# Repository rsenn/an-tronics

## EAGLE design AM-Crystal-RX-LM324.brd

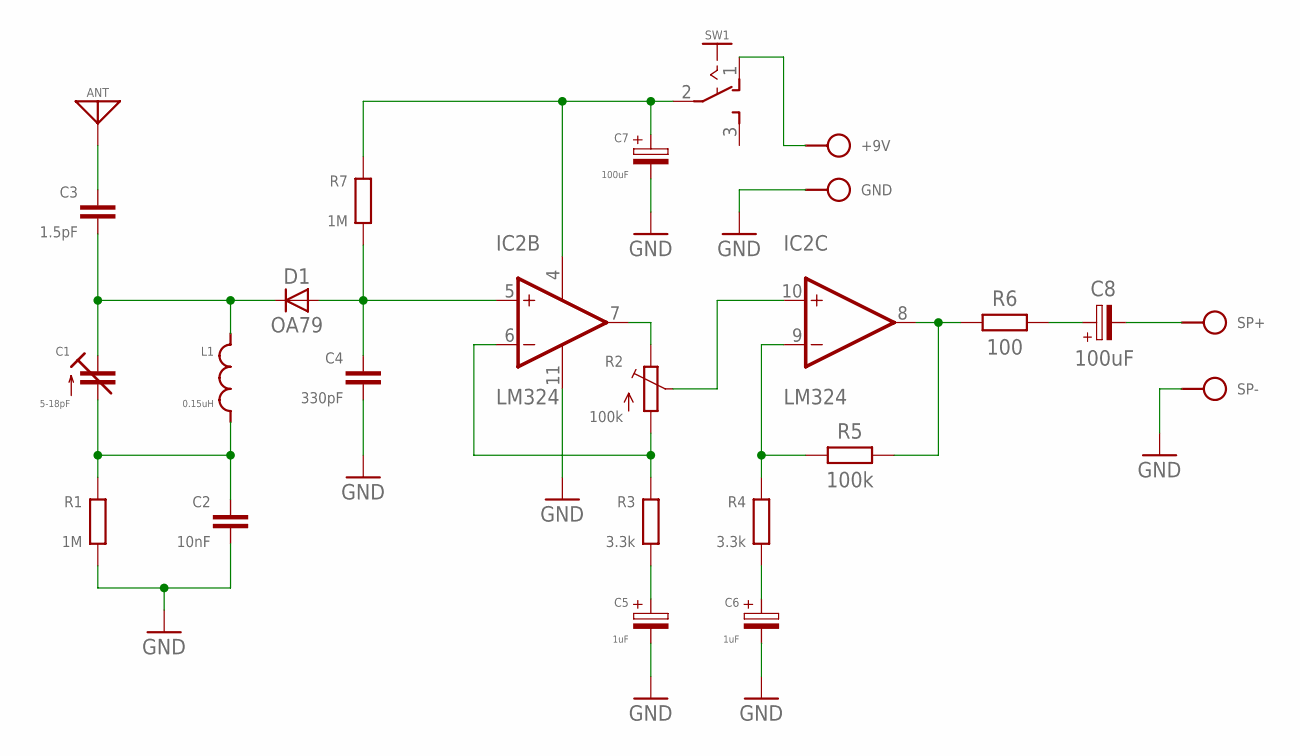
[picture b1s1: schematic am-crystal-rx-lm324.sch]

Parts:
+9V: BAT+; SPAD
ANT: ANT; SPAD
C1: 5-18pF; TRIM-2222-808
C2: 10nF; C050-025X075/V
C3: 1.5pF; C050-020X036
C4: 330pF; C050-024X044/V
C5: 1uF; E2.5-4/V
C6: 1uF; E2,5-3
C7: 100uF; E5-5/V
C8: 100uF; E2,5-5/V
D1: OA79; OA79-18/V
GND: BAT-; SPAD
IC2: LM324; DIL14
L1: 0.15uH; L-04-5/5
R1, R7: 1M; 0202/7-V
R2: 100k; B64Y
R3: 3.3k; 0202/7
R4: 3.3k; 0202/7-V
R5: 100k; 0202/7-V
R6: 100; 0202/7-V
SP+: SPKR+; SPAD
SP-: SPKR-; SPAD
SW1: SL-SW-1P-2T-H; SLSW-1P2T-H

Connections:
A: IC2.7 (OUT), R2.E
E: IC2.6 (-IN), R2.A, R3.2
GND: C2.2, C4.2, C5.-, C6.-, C7.-, GND.1, IC2.11 (V-), R1.1, SP-.1
unnamed: C4.1, D1.A, IC2.5 (+IN), R7.1
unnamed: C7.+, IC2.4 (V+), R7.2, SW1.2
unnamed: C1.1 (A), C2.1, L1.1, R1.2
unnamed: C1.2 (E), C3.2, D1.C, L1.2
unnamed: ANT.1, C3.1
unnamed: IC2.8 (OUT), R5.1, R6.2
unnamed: IC2.9 (-IN), R4.2, R5.2
unnamed: C5.+, R3.1
unnamed: C6.+, R4.1
unnamed: C8.+, R6.1
unnamed: C8.-, SP+.1
unnamed: +9V.1, SW1.1 (O)
S: IC2.10 (+IN), R2.S

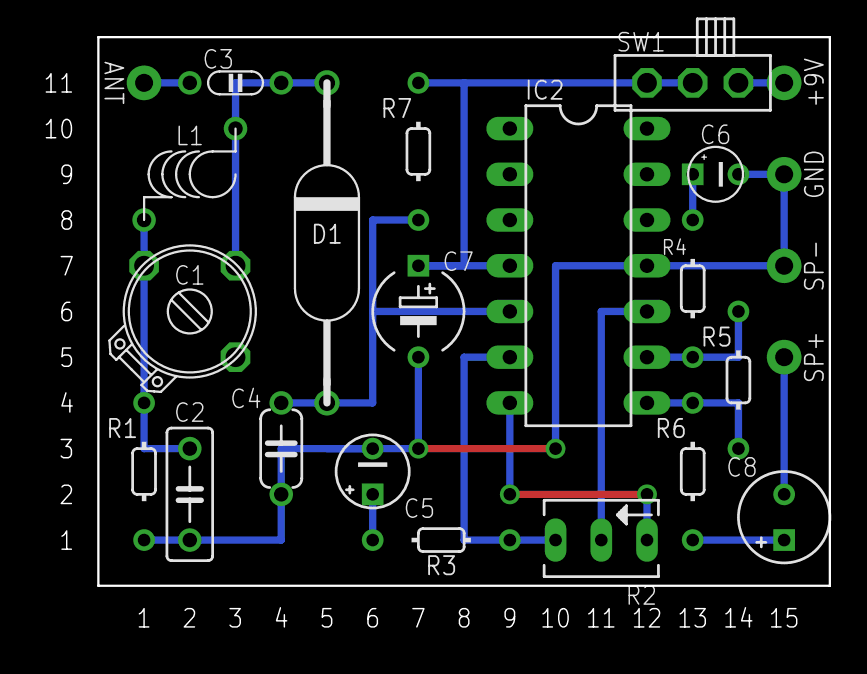
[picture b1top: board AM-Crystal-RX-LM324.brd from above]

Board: 2 copper layers, 40.6 x 30.5 mm, 24 parts (0 on the bottom side), 16 nets.

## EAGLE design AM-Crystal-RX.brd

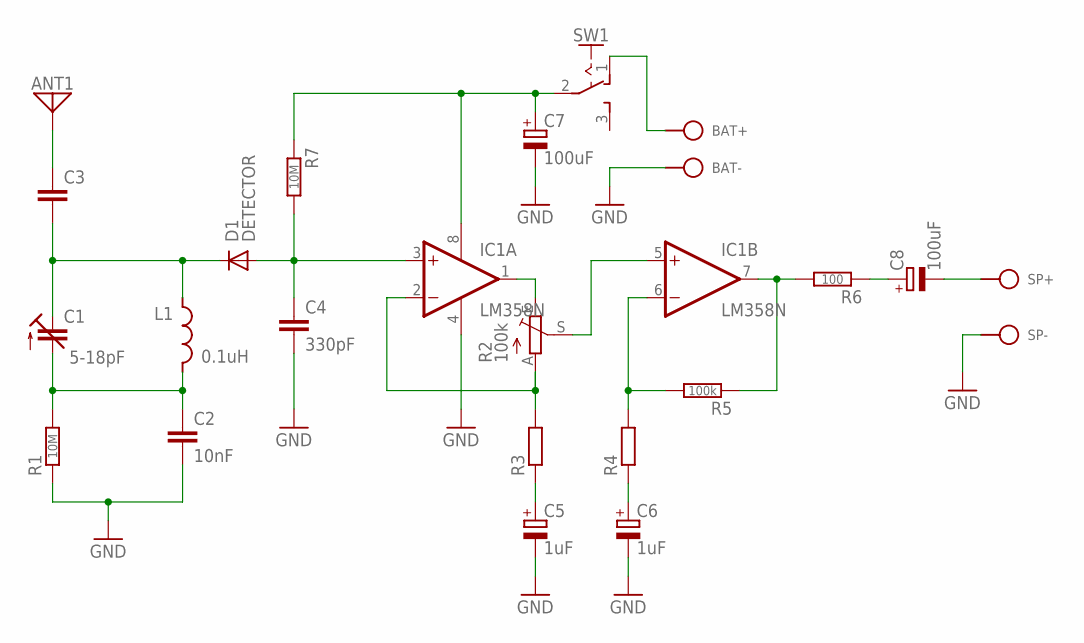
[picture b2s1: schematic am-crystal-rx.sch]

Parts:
ANT1: ANT; SPAD
BAT+: BAT+; SPAD
BAT-: BAT-; SPAD
C1: 5-18pF; TRIM-2222-808
C2: 10nF; C050-025X075
C3: C025-015X024
C4: 330pF; C050-024X044
C5, C6: 1uF; E2,5-3
C7, C8: 100uF; E2,5-5
D1: DETECTOR; DO34-10
IC1: LM358N; DIL08
L1: 0.1uH; L-04/10
R1: 10M; 0202/7-V
R2: 100k; B64Y
R3, R4: R0202/7; 0202/7
R5: 100k; 0202/7
R6: 100; 0202/7
R7: 10M; 0202/7
SP+: SPKR+; SPAD
SP-: SPKR-; SPAD
SW1: SL-SW-1P-2T-H; SLSW-1P2T-H

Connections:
GND: BAT-.1, C2.2, C4.2, C5.-, C6.-, C7.-, IC1.4 (V-), R1.1, SP-.1
unnamed: C4.1, D1.A, IC1.3 (+IN), R7.2
unnamed: C7.+, IC1.8 (V+), R7.1, SW1.2
unnamed: C1.2 (E), C2.1, L1.2, R1.2
unnamed: IC1.2 (-IN), R2.A, R3.2
unnamed: C1.1 (A), C3.2, D1.C, L1.1
unnamed: ANT1.1, C3.1
unnamed: IC1.1 (OUT), R2.E
unnamed: IC1.5 (+IN), R2.S
unnamed: IC1.7 (OUT), R5.1, R6.2
unnamed: IC1.6 (-IN), R4.2, R5.2
unnamed: C5.+, R3.1
unnamed: C6.+, R4.1
unnamed: C8.+, R6.1
unnamed: C8.-, SP+.1
unnamed: BAT+.1, SW1.1 (O)

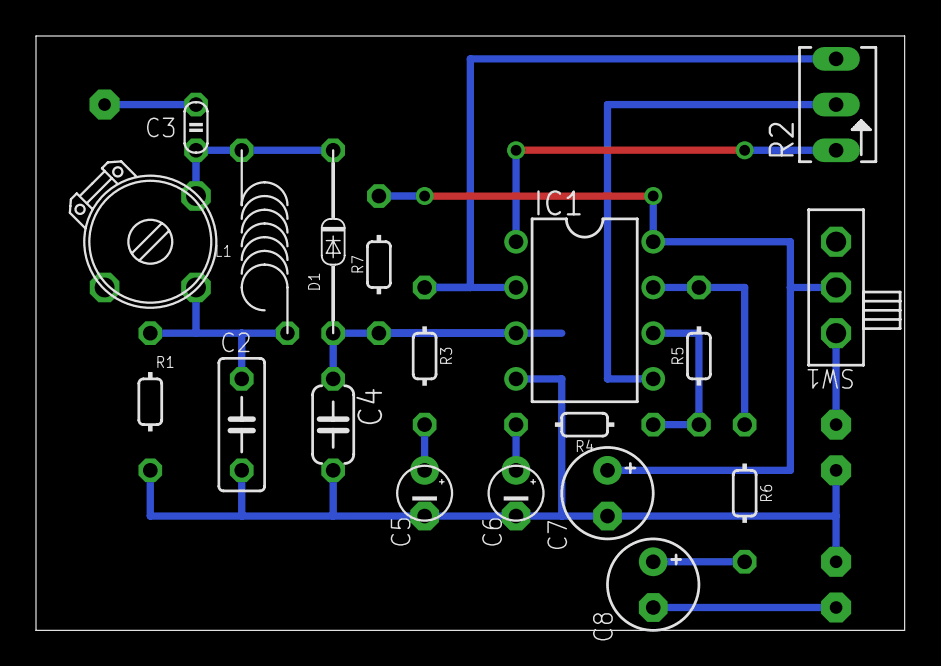
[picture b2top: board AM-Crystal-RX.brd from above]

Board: 2 copper layers, 48.3 x 33.0 mm, 24 parts (0 on the bottom side), 16 nets.

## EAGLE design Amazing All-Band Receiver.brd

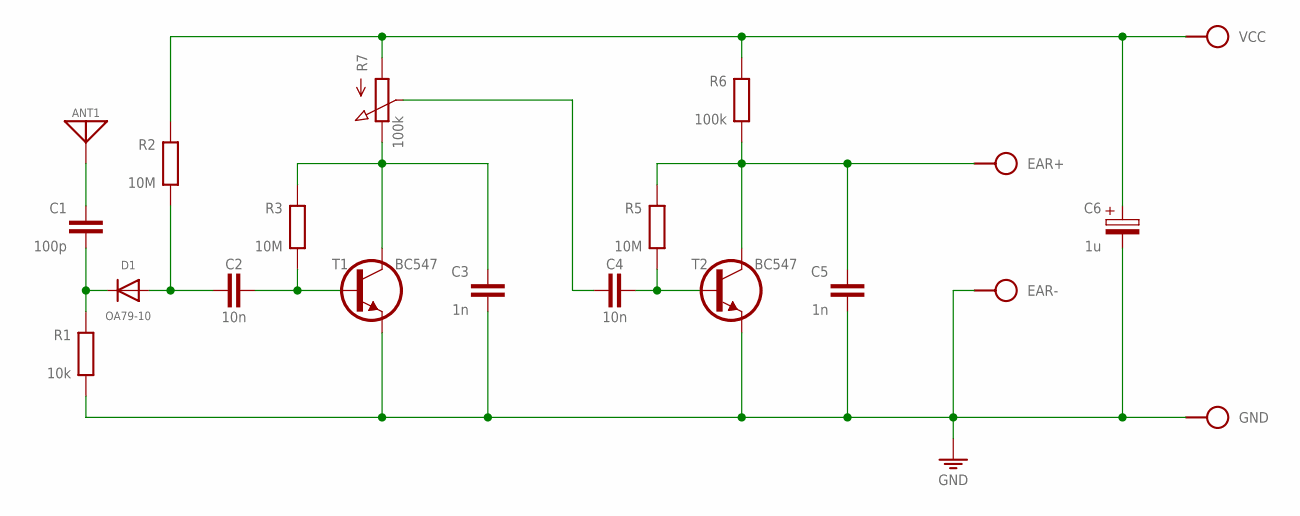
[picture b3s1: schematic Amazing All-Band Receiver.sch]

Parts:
ANT1: ANT; SPAD
C1: 100p; C050-020X036/V
C2, C4: 10n; C050-025X075
C3, C5: 1n; C050-025X075
C6: 1u; E2,5-3
D1: OA79-10; DO34-7V
EAR+: SPAD
EAR-: SPAD
GND: SPAD
R1: 10k; 0202/7-V
R2: 10M; 0202/7
R3, R5: 10M; 0202/7-V
R6: 100k; 0202/7-V
R7: 100k; POT
T1, T2: BC547; TO92-CBE
VCC: SPAD

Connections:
AC: C1.2, D1.C, R1.2
ANT: ANT1.1, C1.1
DC: C2.2, D1.A, R2.1
GND: C3.2, C5.2, C6.-, EAR-.1, GND.1, R1.1, T1.E, T2.E
I1: C2.1, R3.1, T1.B
I2: C4.1, R5.1, T2.B
O1: C3.1, R3.2, R7.3 (E), T1.C
O2: C5.1, EAR+.1, R5.2, R6.1, T2.C
VCC: C6.+, R2.2, R6.2, R7.1 (A), VCC.1
VO1: C4.2, R7.2 (S)

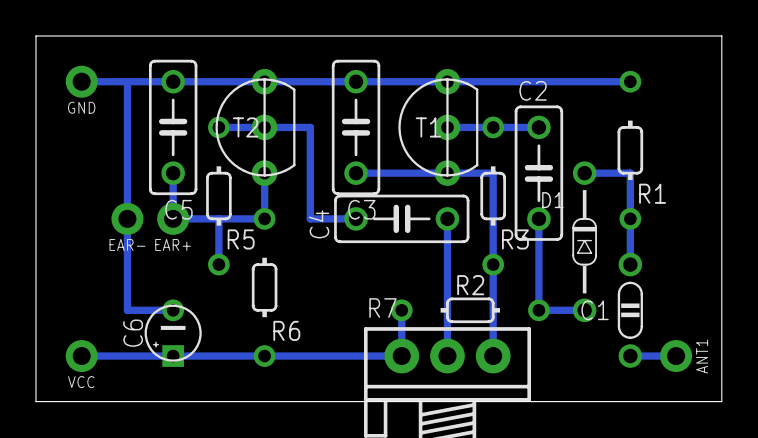
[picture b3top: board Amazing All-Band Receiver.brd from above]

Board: 2 copper layers, 38.1 x 20.3 mm, 20 parts (0 on the bottom side), 10 nets.

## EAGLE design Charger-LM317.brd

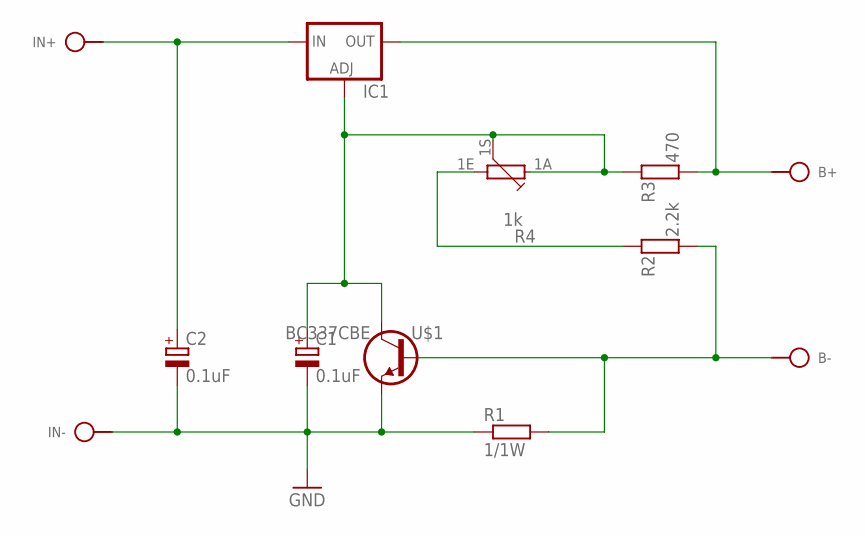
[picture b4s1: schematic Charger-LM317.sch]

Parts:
B+: SPAD
B-: SPAD
C1: 0.1uF; E5-4
C2: 0.1uF; E2,5-4
IC1: LM317TL; 317TL
IN+: SPAD
IN-: SPAD
R1: 1/1W; 0309/12
R2: 2.2k; 0204/10
R3: 470; 0204/10
R4: 1k; PC16S
U$1: BC337CBE; TO92-CBE

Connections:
GND: C1.-, C2.-, IN-.1, R1.1, U$1.E
unnamed: B-.1, R1.2, R2.1, U$1.B
unnamed: R2.2, R4.1E
unnamed: C1.+, IC1.1 (ADJ), R3.2, R4.1A, R4.1S, U$1.C
unnamed: B+.1, IC1.2 (OUT), R3.1
unnamed: C2.+, IC1.3 (IN), IN+.1

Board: 2 copper layers, 12 parts (0 on the bottom side), 6 nets, no tracks yet.

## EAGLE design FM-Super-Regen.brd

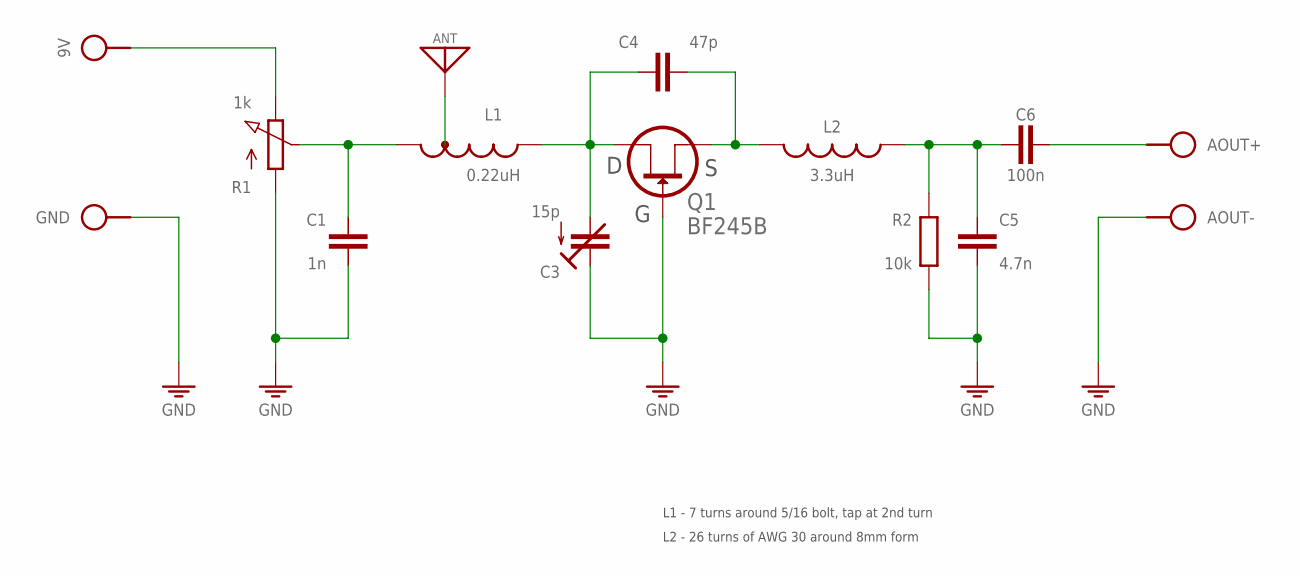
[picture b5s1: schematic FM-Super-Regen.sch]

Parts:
9V: SPAD
ANT: ANT; SPAD
AOUT+: SPAD
AOUT-: SPAD
C1: 1n; C050-020X036/V
C3: 15p; TRIM-2222-808
C4: 47p; C025-015X024
C5: 4.7n; C050-020X036
C6: 100n; C050-020X036
GND: SPAD
L1: 0.22uH; L-08/7V-TAP1
L2: 3.3uH; L-BODY
Q1: BF245B; TO92
R1: 1k; POT-V
R2: 10k; 0204/10

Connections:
GND: AOUT-.1, C1.2, C3.1 (E), C5.2, GND.1, Q1.1 (G), R1.A, R2.1
unnamed: 9V.1, R1.E
unnamed: C3.2 (A), C4.1, L1.2, Q1.3 (D)
unnamed: C1.1, L1.1, R1.S
unnamed: ANT.1, L1.T
unnamed: C4.2, L2.3 (2), Q1.2 (S)
unnamed: C5.1, C6.1, L2.4 (1), R2.2
unnamed: AOUT+.1, C6.2

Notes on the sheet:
L1 - 7 turns around 5/16 bolt, tap at 2nd turn
L2 - 26 turns of AWG 30 around 8mm form

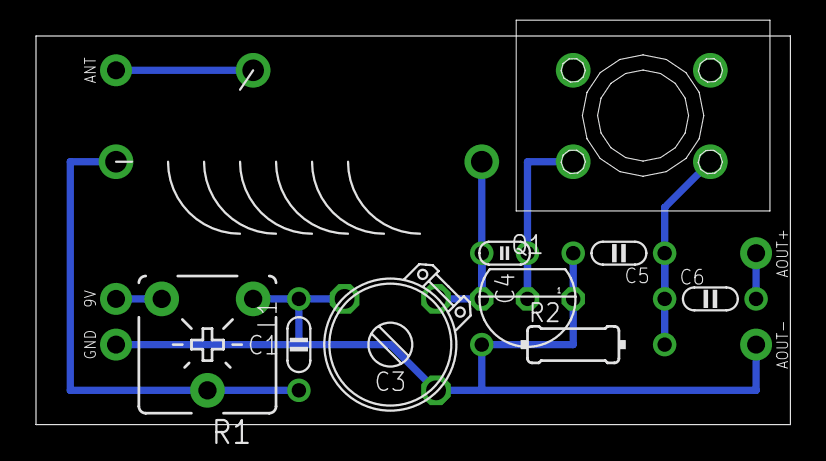
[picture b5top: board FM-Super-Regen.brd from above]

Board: 2 copper layers, 41.9 x 21.6 mm, 15 parts (0 on the bottom side), 8 nets.

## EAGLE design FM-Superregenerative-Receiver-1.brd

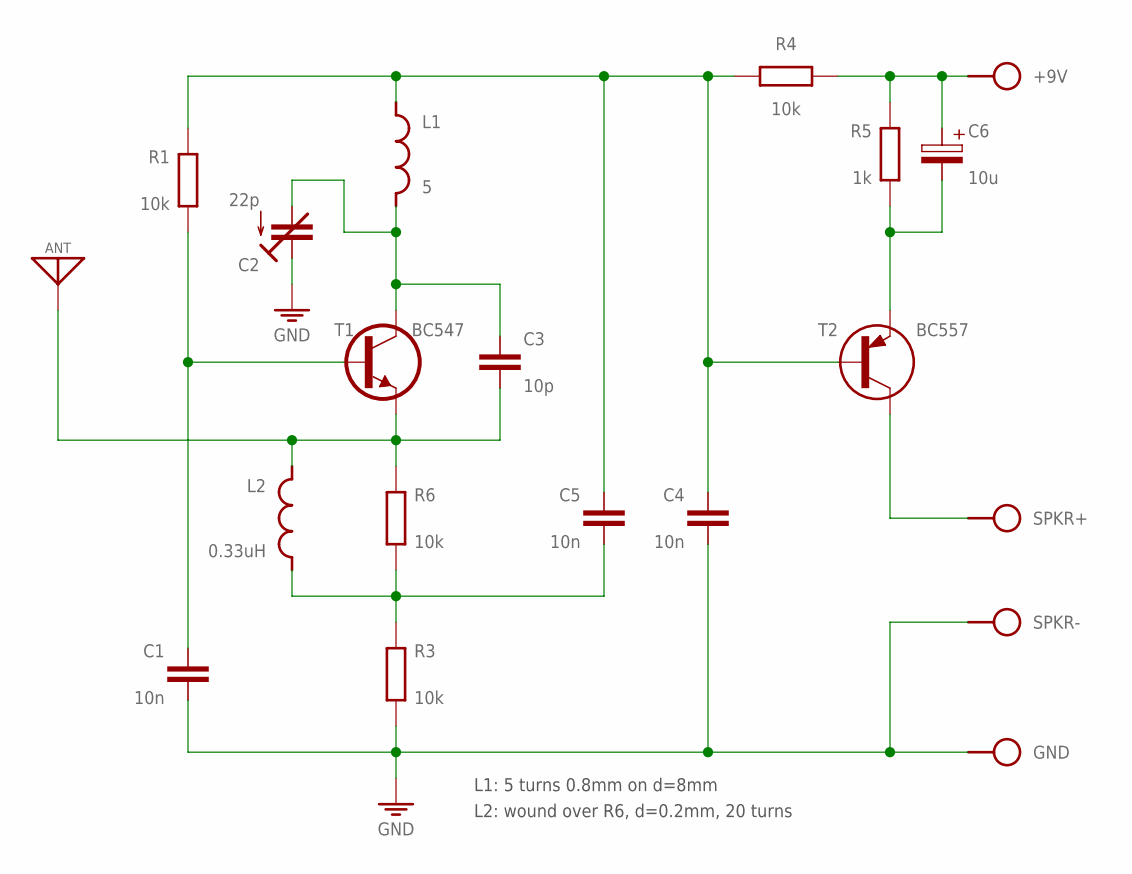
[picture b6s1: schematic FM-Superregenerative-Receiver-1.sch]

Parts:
+9V: SPAD
ANT: ANT; SPAD
C1, C4, C5: 10n; C050-025X075
C2: 22p; TRIM-2222-808
C3: 10p; C050-020X036
C6: 10u; E2,5-3
GND: SPAD
L1: 5; L-02/7V
L2: 0.33uH; L-02/7V
R1, R4: 10k; 0202/7
R3, R6: 10k; 0202/7-V
R5: 1k; 0202/7-V
SPKR+: SPAD
SPKR-: SPAD
T1: BC547; TO92-CBE
T2: BC557; TO92-CBE

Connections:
GND: C1.2, C2.1 (E), C4.2, GND.1, R3.1, SPKR-.1
unnamed: C1.1, R1.1, T1.B
unnamed: C6.-, R5.1, T2.E
unnamed: C5.2, L2.2, R3.2, R6.1
unnamed: ANT.1, C3.2, L2.1, R6.2, T1.E
unnamed: C4.1, C5.1, L1.1, R1.2, R4.2, T2.B
unnamed: C2.2 (A), C3.1, L1.2, T1.C
unnamed: +9V.1, C6.+, R4.1, R5.2
unnamed: SPKR+.1, T2.C

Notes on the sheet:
L1: 5 turns 0.8mm on d=8mm
L2: wound over R6, d=0.2mm, 20 turns

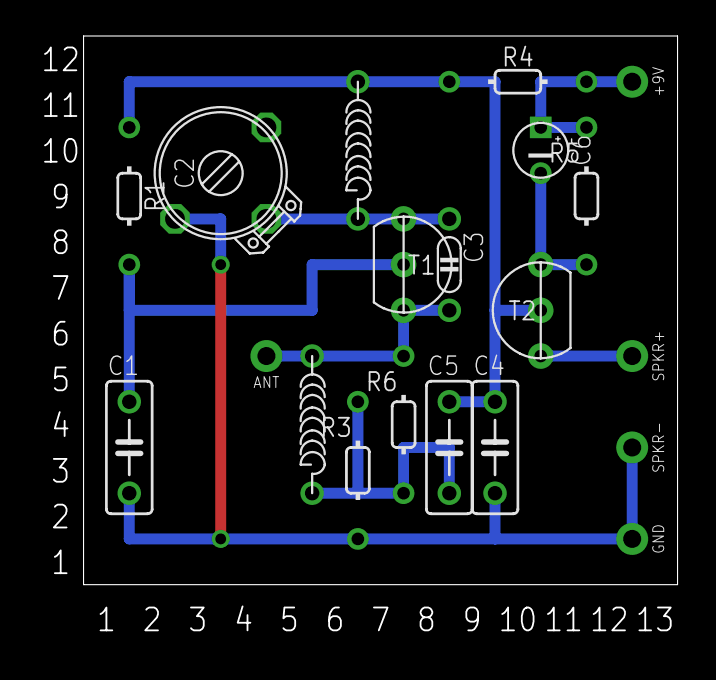
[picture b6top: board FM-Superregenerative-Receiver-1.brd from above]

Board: 2 copper layers, 33.0 x 30.5 mm, 20 parts (0 on the bottom side), 9 nets.

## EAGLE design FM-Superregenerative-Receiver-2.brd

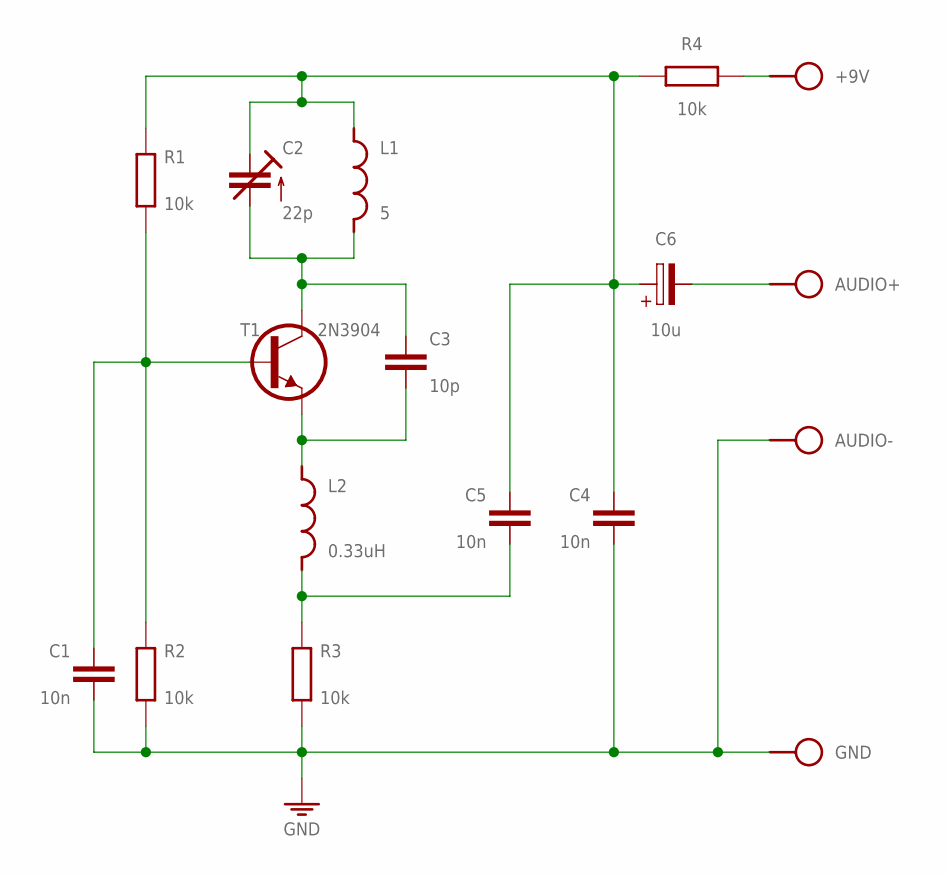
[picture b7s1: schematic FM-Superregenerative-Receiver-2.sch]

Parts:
+9V: SPAD
AUDIO+: SPAD
AUDIO-: SPAD
C1, C4, C5: 10n; C050-025X075
C2: 22p; TRIM-2222-808
C3: 10p; C050-020X036
C6: 10u; E2,5-3
GND: SPAD
L1: 5; L-02/5V
L2: 0.33uH; L-02/5V
R1, R2, R3, R4: 10k; 0204/10
T1: 2N3904; TO92

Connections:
GND: AUDIO-.1, C1.2, C4.2, GND.1, R2.1, R3.1
unnamed: C1.1, R1.1, R2.2, T1.2 (B)
unnamed: AUDIO+.1, C6.-
unnamed: C5.2, L2.2, R3.2
unnamed: C3.2, L2.1, T1.1 (E)
unnamed: C2.2 (A), C3.1, L1.2, T1.3 (C)
unnamed: +9V.1, R4.1
unnamed: C2.1 (E), C2.3 (E), C4.1, C5.1, C6.+, L1.1, R1.2, R4.2

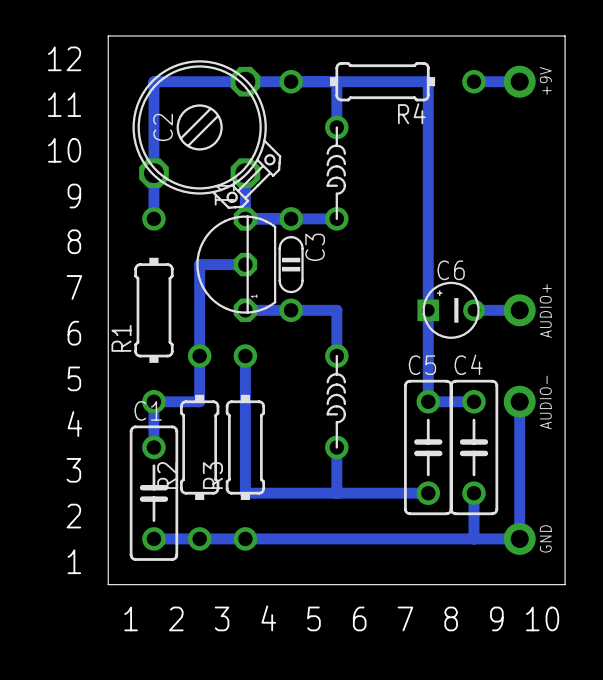
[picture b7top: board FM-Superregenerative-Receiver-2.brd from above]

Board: 2 copper layers, 25.4 x 30.5 mm, 17 parts (0 on the bottom side), 8 nets.
